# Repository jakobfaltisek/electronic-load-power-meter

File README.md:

View this project on [CADLAB.io](https://cadlab.io/project/1274). 

# electronic-load-power-meter

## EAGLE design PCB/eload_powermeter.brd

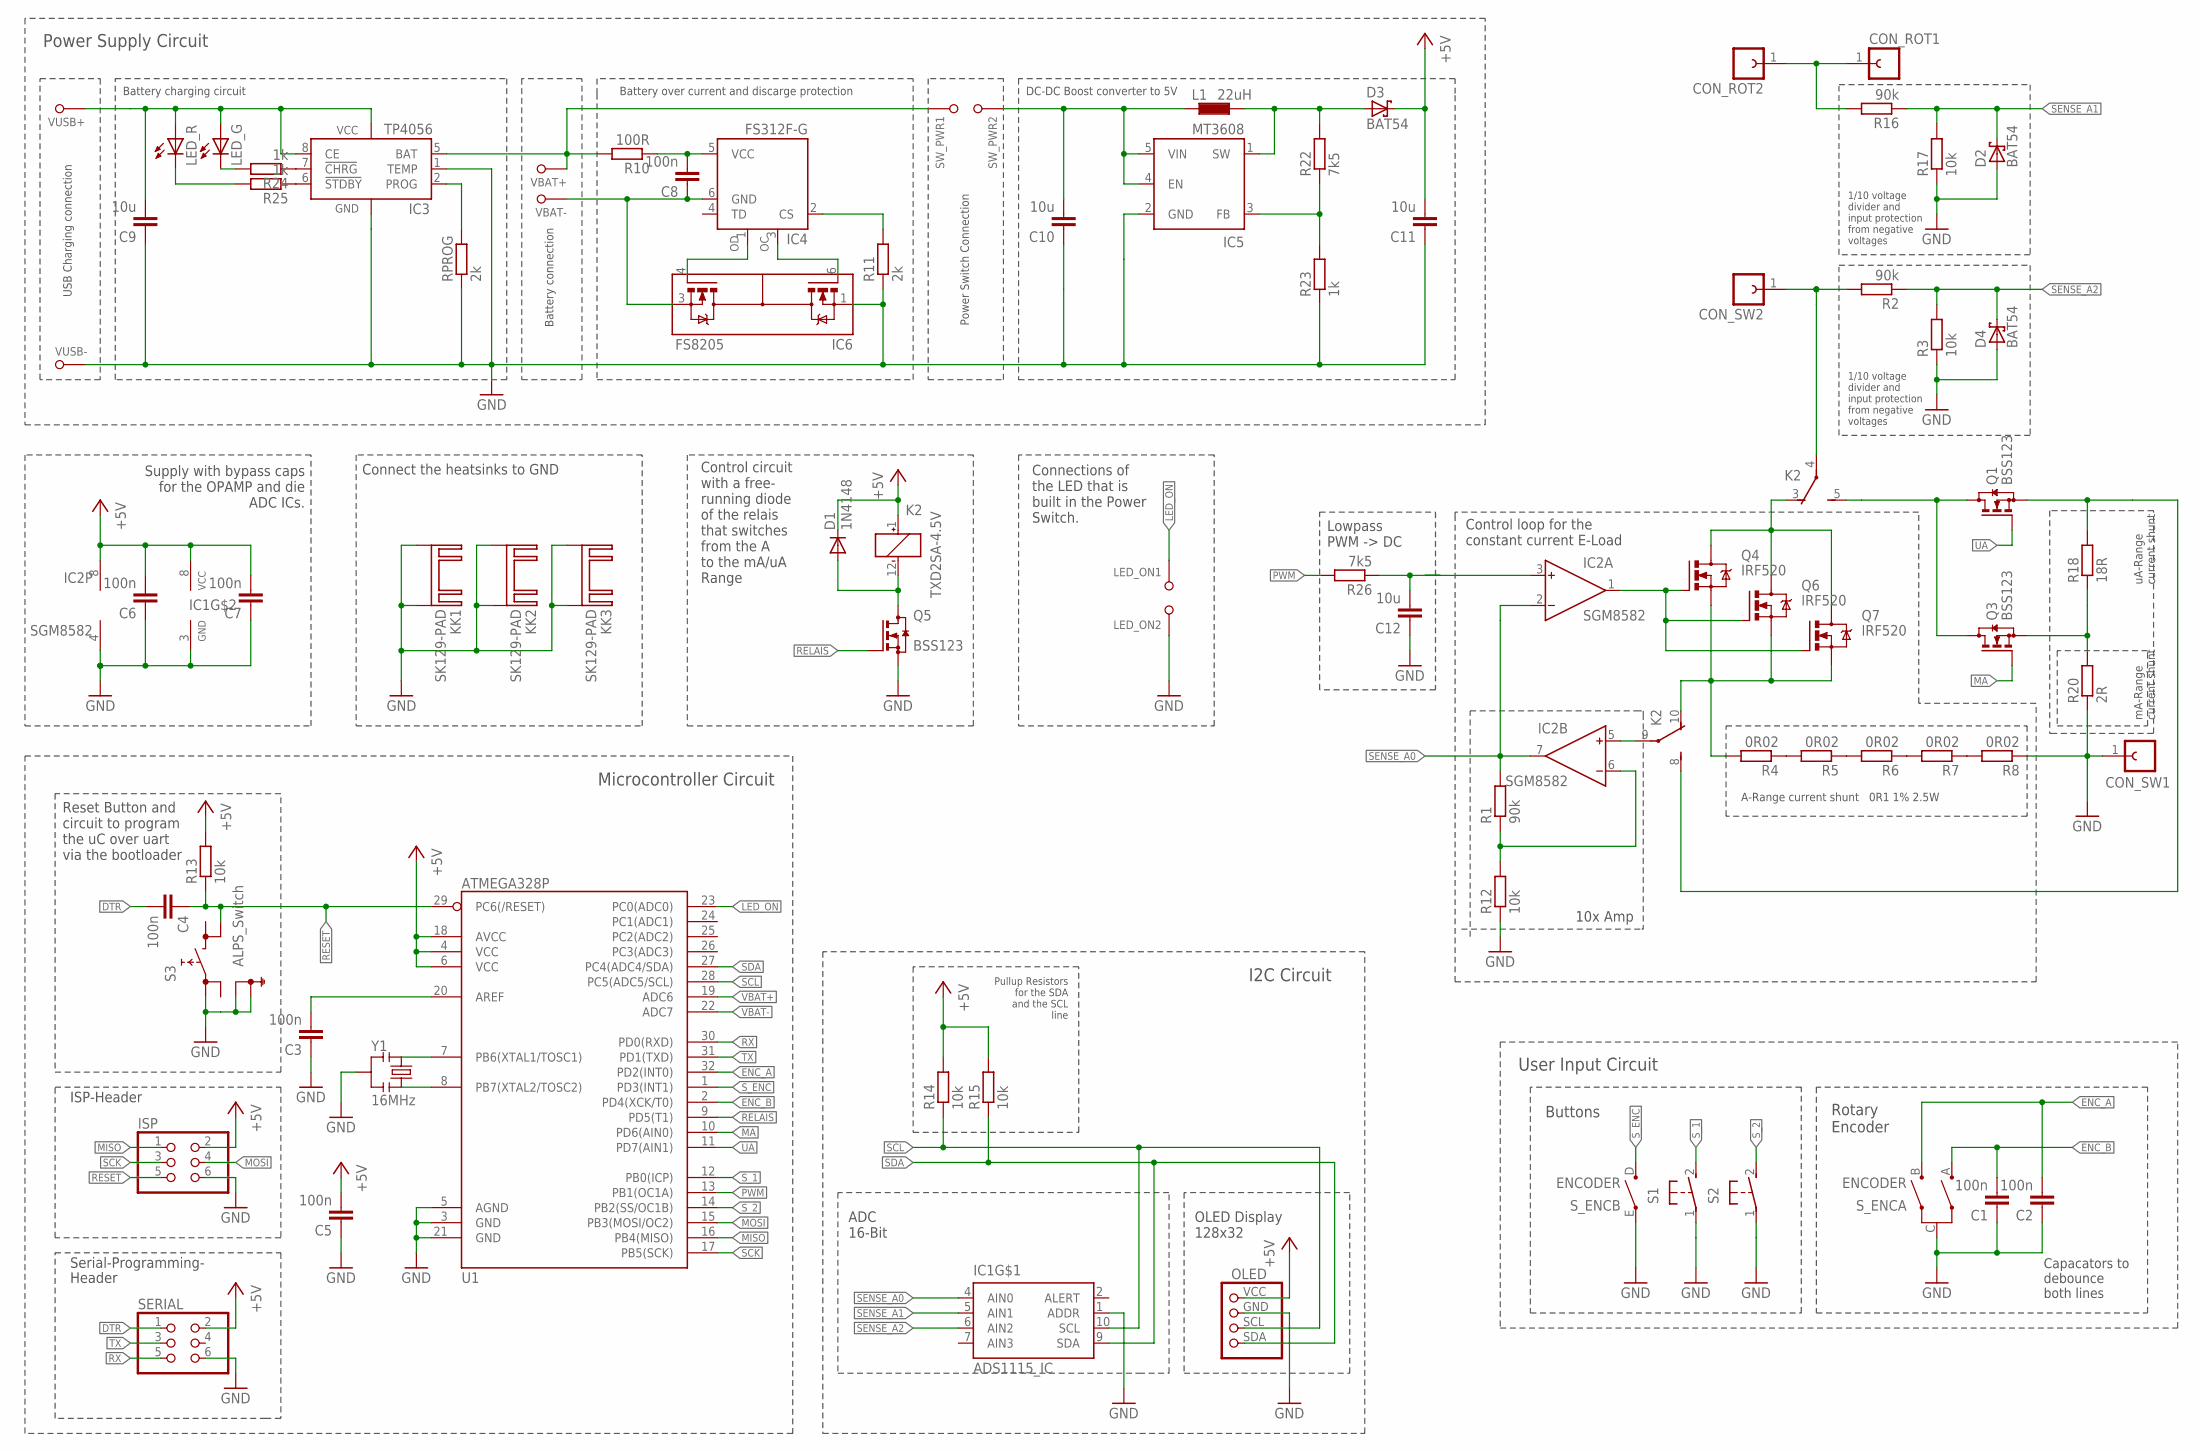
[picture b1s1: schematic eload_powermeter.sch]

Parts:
C1, C2, C3, C4, C5, C6, C7, C8: 100n; C0603
C9, C10, C11, C12: 10u; C0603
CON_ROT1, CON_ROT2: BANANEN_BUCHSE; BANANENBUCHSE
CON_SW1, CON_SW2: BANANEN_BUCHSE; BANANENBUCHSE
D1: 1N4148; SOD123
D2, D3, D4: BAT54; SOT23
IC1: ADS1115_IC; MSOP10
IC2: SGM8582; SO8
IC3: TP4056; SOP08
IC4: FS312F-G; SOT23-6
IC5: MT3608; SOT23-6
IC6: FS8205; SOT23-6
ISP: PINHD-2X3_SMD; 2X03
K2: TXD2SA-4.5V; TXD2SA
KK1, KK2, KK3: SK129-PAD; SK129
L1: 22uH; R1210
LED_G: LED_REVERSE_MOUNTSMT1206_REVERSE; 1206_LED_REVERSE_MOUNT
LED_ON1, LED_ON2: SOLDER_PAD
LED_R: LED_REVERSE_MOUNTSMT1206_REVERSE; 1206_LED_REVERSE_MOUNT
OLED: OLED_128X32; 1X04_OLED
Q1, Q3, Q5: BSS123; SOT23
Q4, Q6, Q7: IRF520; TO220BV
R1, R2, R16: 90k; R0603
R3, R12, R13, R14, R15, R17: 10k; R0603
R4, R5, R6, R7, R8: 0R02; R1206
R10: 100R; R0603
R11: 2k; R0603
R18: 18R; R0603
R20: 2R; R0603
R22, R26: 7k5; R0603
R23, R24, R25: 1k; R0603
RPROG: 2k; R0603
S1, S2: PUSH_BUTTON_ALPS; B3F-31XX
S3: ALPS_Switch; SKHMPXE010
SERIAL: PINHD-2X3_SMD; 2X03
SW_PWR1, SW_PWR2: SOLDER_PAD
S_ENC: ENCODER; CI-11
U1: ATMEGA328P; TQFP32-08
VBAT+: SOLDER_PAD
VBAT-: SOLDER_PAD
VUSB+: SOLDER_PAD
VUSB-: SOLDER_PAD
Y1: 16MHz; RESONATOR-SMD-1:1

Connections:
+5V: C5.2, C6.2, C7.2, C11.2, D1.C, D3.3 (C), IC1.8 (VCC), IC2.8 (V+), ISP.2, K2.1 (+), OLED.VCC (VDD), R13.2, R14.2, R15.2, SERIAL.2, U1.4 (VCC), U1.6 (VCC), U1.18 (AVCC)
DTR: C4.2, SERIAL.1
ENC_A: C2.2, S_ENC.B, U1.32 (PD2(INT0))
ENC_B: C1.2, S_ENC.A, U1.2 (PD4(XCK/T0))
GND: C1.1, C2.1, C3.1, C5.1, C6.1, C7.1, C9.1, C10.1, C11.1, C12.1, CON_SW1.1, D2.1 (A), D4.1 (A), IC1.1 (ADDR), IC1.3 (GND), IC2.4 (V-), IC3.1 (TEMP), IC3.3 (GND), IC5.2 (GND), IC6.1 (S1), ISP.6, KK1.A2,5, KK1.B2,5, KK2.A2,5, KK2.B2,5, KK3.A2,5, KK3.B2,5, LED_ON2.P$1, OLED.GND, Q5.2 (S), R3.1, R8.1, R11.1, R12.1, R17.1, R20.1, R23.1, RPROG.1, S1.1, S2.1, S3.1 (3.1), S3.5 (SH1), S3.6 (SH2), SERIAL.6, S_ENC.C, S_ENC.E, U1.3 (GND), U1.5 (AGND), U1.21 (GND), VUSB-.P$1, Y1.2
LED_ON: LED_ON1.P$1, U1.23 (PC0(ADC0))
MA: Q3.1 (G), U1.10 (PD6(AIN0))
MISO: ISP.1, U1.16 (PB4(MISO))
MOSI: ISP.4, U1.15 (PB3(MOSI/OC2))
unnamed: CON_ROT1.1, CON_ROT2.1, R16.2
unnamed: IC2.1 (OUT), Q4.G, Q6.G, Q7.G
unnamed: Q3.2 (S), R18.1, R20.2
unnamed: K2.5 (S), Q1.3 (D), Q3.3 (D)
unnamed: R4.1, R5.2
unnamed: K2.10 (O), Q4.S, Q6.S, Q7.S, R4.2
unnamed: C12.2, IC2.3 (IN+), R26.1
unnamed: K2.3 (O), Q4.D, Q6.D, Q7.D
unnamed: D1.A, K2.12 (-), Q5.3 (D)
unnamed: R5.1, R6.2
unnamed: U1.7 (PB6(XTAL1/TOSC1)), Y1.1
unnamed: IC2.5 (IN+), K2.9
unnamed: CON_SW2.1, K2.4, R2.2
unnamed: U1.8 (PB7(XTAL2/TOSC2)), Y1.3
unnamed: C8.2, IC4.5 (VCC), R10.1
unnamed: R6.1, R7.2
unnamed: R7.1, R8.2
unnamed: D3.1 (A), IC5.1 (SW), L1.2, R22.2
unnamed: IC4.1 (OD), IC6.4 (G2)
unnamed: IC3.2 (PROG), RPROG.2
unnamed: IC4.3 (OC), IC6.6 (G1)
unnamed: C10.2, IC5.4 (EN), IC5.5 (VIN), L1.1, SW_PWR2.P$1
unnamed: IC4.2 (CS), R11.2
unnamed: IC5.3 (FB), R22.1, R23.2
unnamed: IC3.7 (!CHRG), R24.1
unnamed: IC3.6 (!STDBY), R25.1
unnamed: LED_G.C, R24.2
unnamed: LED_R.C, R25.2
unnamed: C3.2, U1.20 (AREF)
unnamed: IC2.6 (IN-), R1.1, R12.2
unnamed: K2.8 (S), Q1.2 (S), R18.2
PWM: R26.2, U1.13 (PB1(OC1A))
RELAIS: Q5.1 (G), U1.9 (PD5(T1))
RESET: C4.1, ISP.5, R13.1, S3.4 (4.2), U1.29 (PC6(/RESET))
RX: SERIAL.5, U1.30 (PD0(RXD))
SCK: ISP.3, U1.17 (PB5(SCK))
SCL: IC1.10 (SCL), OLED.SCL, R14.1, U1.28 (PC5(ADC5/SCL))
SDA: IC1.9 (SDA), OLED.SDA, R15.1, U1.27 (PC4(ADC4/SDA))
SENSE_A0: IC1.4 (AIN0), IC2.2 (IN-), IC2.7 (OUT), R1.2
SENSE_A1: D2.3 (C), IC1.5 (AIN1), R16.1, R17.2
SENSE_A2: D4.3 (C), IC1.6 (AIN2), R2.1, R3.2
S_1: S1.2 (S), U1.12 (PB0(ICP))
S_2: S2.2 (S), U1.14 (PB2(SS/OC1B))
S_ENC: S_ENC.D, U1.1 (PD3(INT1))
TX: SERIAL.3, U1.31 (PD1(TXD))
UA: Q1.1 (G), U1.11 (PD7(AIN1))
VBAT+: IC3.5 (BAT), R10.2, SW_PWR1.P$1, U1.19 (ADC6), VBAT+.P$1
VBAT-: C8.1, IC4.6 (GND), IC6.3 (S2), U1.22 (ADC7), VBAT-.P$1
VUSB: C9.2, IC3.4 (VCC), IC3.8 (CE), LED_G.A, LED_R.A, VUSB+.P$1

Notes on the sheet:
Microcontroller Circuit
ISP-Header
Serial-Programming-
Header
10x Amp
Lowpass PWM -> DC
1/10 voltage divider and input protection from negative voltages
A-Range current shunt 0R1 1% 2.5W
mA-Range current shunt
uA-Range current shunt
Control loop for the constant current E-Load
Reset Button and circuit to program the uC over uart via the bootloader
Supply with bypass caps for the OPAMP and die ADC ICs.
Connect the heatsinks to GND
Control circuit with a free- running diode of the relais that switches from the A to the mA/uA Range
Battery charging circuit
Battery over current and discarge protection
DC-DC Boost converter to 5V
USB Charging connection
Battery connection
Power Switch Connection
Power Supply Circuit
I2C Circuit
Pullup Resistors for the SDA and the SCL line
ADC 16-Bit
OLED Display 128x32
Buttons
Rotary Encoder
User Input Circuit
Capacators to debounce both lines
Connections of the LED that is built in the Power Switch.

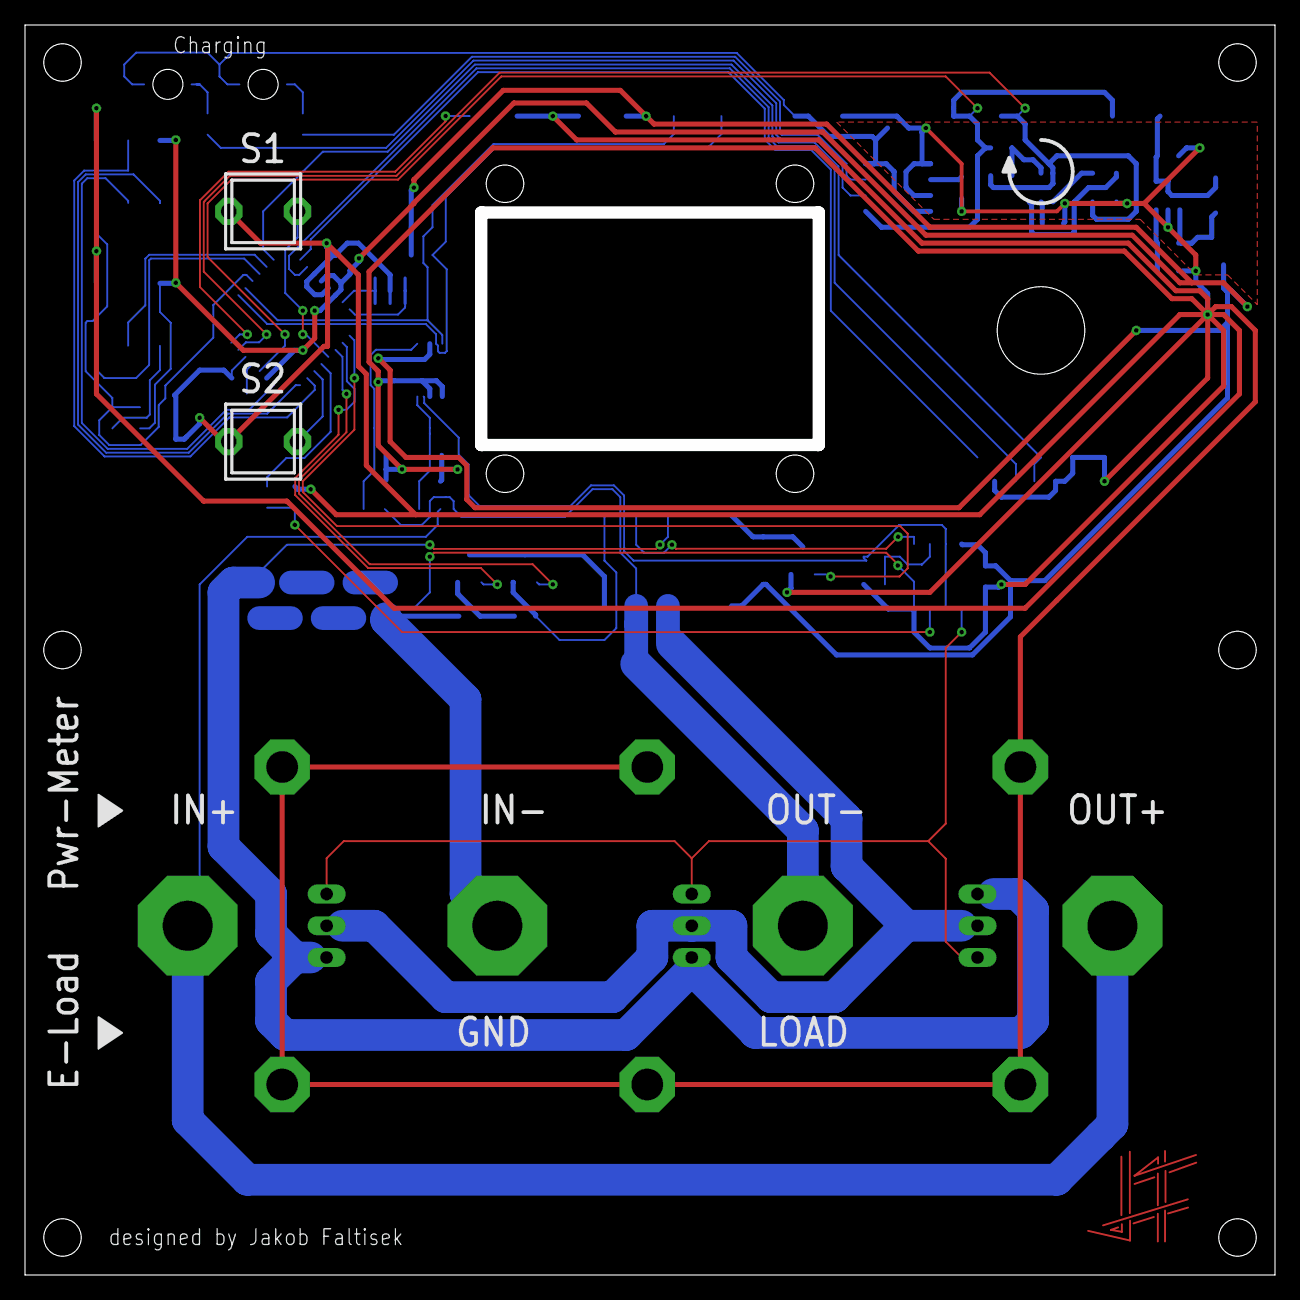
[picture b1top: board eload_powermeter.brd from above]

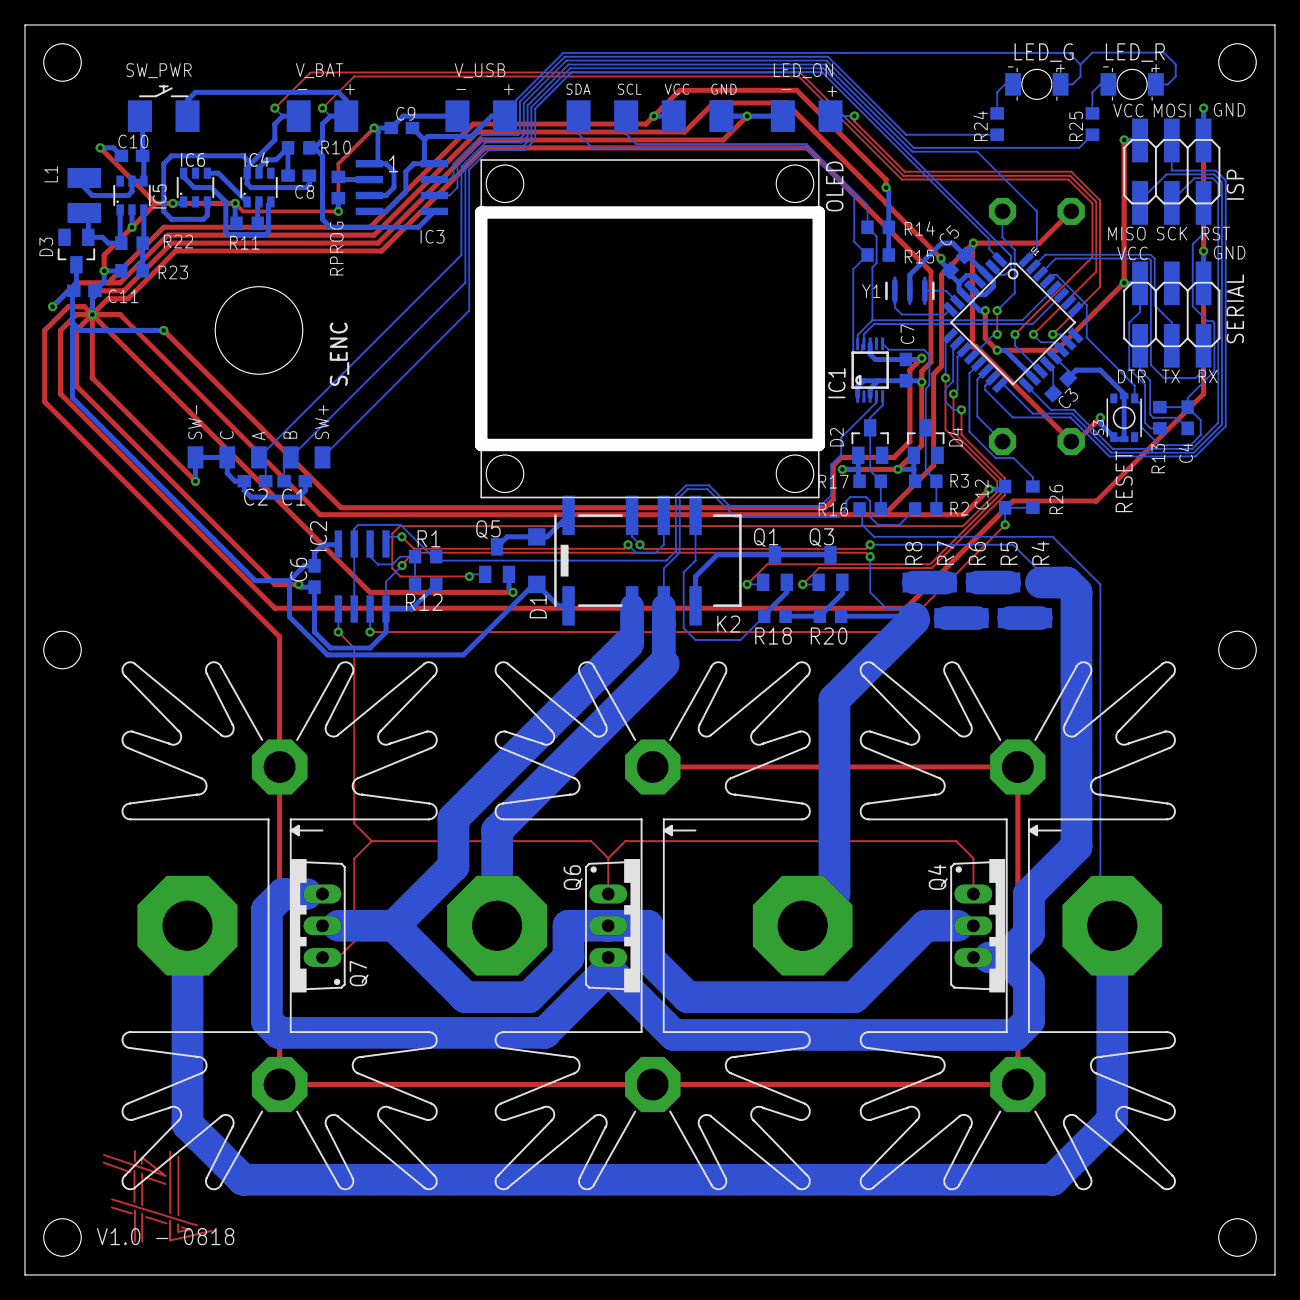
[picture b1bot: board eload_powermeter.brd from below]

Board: 2 copper layers, 100.0 x 100.0 mm, 80 parts (72 on the bottom side), 58 nets.

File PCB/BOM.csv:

"Part";"Value";"Device";"Package";"Description";"MF";"MPN";"OC_FARNELL";"OC_NEWARK";"SPICEPREFIX";
"C1";"100n";"C-EUC0603";"C0603";"CAPACITOR, European symbol";"";"";"";"";"C";
"C2";"100n";"C-EUC0603";"C0603";"CAPACITOR, European symbol";"";"";"";"";"C";
"C3";"100n";"C-EUC0603";"C0603";"CAPACITOR, European symbol";"";"";"";"";"C";
"C4";"100n";"C-EUC0603";"C0603";"CAPACITOR, European symbol";"";"";"";"";"C";
"C5";"100n";"C-EUC0603";"C0603";"CAPACITOR, European symbol";"";"";"";"";"C";
"C6";"100n";"C-EUC0603";"C0603";"CAPACITOR, European symbol";"";"";"";"";"C";
"C7";"100n";"C-EUC0603";"C0603";"CAPACITOR, European symbol";"";"";"";"";"C";
"C8";"100n";"C-EUC0603";"C0603";"CAPACITOR, European symbol";"";"";"";"";"C";
"C9";"10u";"C-EUC0603";"C0603";"CAPACITOR, European symbol";"";"";"";"";"C";
"C10";"10u";"C-EUC0603";"C0603";"CAPACITOR, European symbol";"";"";"";"";"C";
"C11";"10u";"C-EUC0603";"C0603";"CAPACITOR, European symbol";"";"";"";"";"C";
"C12";"10u";"C-EUC0603";"C0603";"CAPACITOR, European symbol";"";"";"";"";"C";
"CON_ROT1";"";"BANANEN_BUCHSE";"BANANENBUCHSE";"FEMALE HEADER";"";"";"";"";"";
"CON_ROT2";"";"BANANEN_BUCHSE";"BANANENBUCHSE";"FEMALE HEADER";"";"";"";"";"";
"CON_SW1";"";"BANANEN_BUCHSE";"BANANENBUCHSE";"FEMALE HEADER";"";"";"";"";"";
"CON_SW2";"";"BANANEN_BUCHSE";"BANANENBUCHSE";"FEMALE HEADER";"";"";"";"";"";
"D1";"1N4148";"MBR0520LT";"SOD123";"SCHOTTKY BARRIER RECTIFIER";"";"";"";"";"";
"D2";"BAT54";"BAT54";"SOT23";"Schottky Diodes";"";"";"";"";"";
"D3";"BAT54";"BAT54";"SOT23";"Schottky Diodes";"";"";"";"";"";
"D4";"BAT54";"BAT54";"SOT23";"Schottky Diodes";"";"";"";"";"";
"IC1";"ADS1115_IC";"ADS1115_IC";"MSOP10";"edit this description";"";"";"";"";"";
"IC2";"SGM8582";"AD826R";"SO8";"High-Speed, Low-Power Dual Operational Amplifier";"ALTERA CORPORATION";"AD826AR";"1651291";"05F7688";"";
"IC3";"TP4056";"TP4056";"SOP08";"edit this description";"";"";"";"";"";
"IC4";"FS312F-G";"FS312F-G";"SOT23-6";"edit this description";"";"";"";"";"";
"IC5";"MT3608";"MT3608";"SOT23-6";"90% EFFICIENT SYNCHRONOUS BOOST CONVERTER WITH 600-mA SWITCH";"";"";"";"";"";
"IC6";"FS8205";"FS8205";"SOT23-6";"";"";"";"";"";"";
"ISP";"";"PINHD-2X3_SMD";"2X03";"PIN HEADER";"";"";"";"";"";
"K2";"TXD2SA-4.5V";"TXD2SA-4.5V";"TXD2SA";"TX Relais NAiS";"";"TXD2SA-4.5V";"unknown";"13P9531";"";
"KK1";"SK129-PAD";"SK129-PAD";"SK129";"HEATSINK manufacturer Fischer/distributor Buerklin";"";"";"";"";"";
"KK2";"SK129-PAD";"SK129-PAD";"SK129";"HEATSINK manufacturer Fischer/distributor Buerklin";"";"";"";"";"";
"KK3";"SK129-PAD";"SK129-PAD";"SK129";"HEATSINK manufacturer Fischer/distributor Buerklin";"";"";"";"";"";
"L1";"22uH";"L_1210";"R1210";"";"";"";"";"";"";
"LED_G";"";"LED_REVERSE_MOUNTSMT1206_REVERSE";"1206_LED_REVERSE_MOUNT";"LED";"";"";"";"";"";
"LED_ON1";"SOLDER_PAD";"SOLDER_PAD";"SOLDER_PAD";"";"";"";"";"";"";
"LED_ON2";"SOLDER_PAD";"SOLDER_PAD";"SOLDER_PAD";"";"";"";"";"";"";
"LED_R";"";"LED_REVERSE_MOUNTSMT1206_REVERSE";"1206_LED_REVERSE_MOUNT";"LED";"";"";"";"";"";
"OLED";"";"OLED_128X32";"1X04_OLED";"PIN HEADER";"";"";"";"";"";
"Q1";"BSS123";"BSS123";"SOT23";"N-CHANNEL MOS FET";"";"";"";"";"";
"Q3";"BSS123";"BSS123";"SOT23";"N-CHANNEL MOS FET";"";"";"";"";"";
"Q4";"IRF520";"IRF520";"TO220BV";"HEXFET Power MOSFET";"";"";"";"";"";
"Q5";"BSS123";"BSS123";"SOT23";"N-CHANNEL MOS FET";"";"";"";"";"";
"Q6";"IRF520";"IRF520";"TO220BV";"HEXFET Power MOSFET";"";"";"";"";"";
"Q7";"IRF520";"IRF520";"TO220BV";"HEXFET Power MOSFET";"";"";"";"";"";
"R1";"90k";"R-EU_R0603";"R0603";"RESISTOR, European symbol";"";"";"";"";"R";
"R2";"90k";"R-EU_R0603";"R0603";"RESISTOR, European symbol";"";"";"";"";"R";
"R3";"10k";"R-EU_R0603";"R0603";"RESISTOR, European symbol";"";"";"";"";"R";
"R4";"0R02";"R-EU_R1206";"R1206";"RESISTOR, European symbol";"";"";"";"";"R";
"R5";"0R02";"R-EU_R1206";"R1206";"RESISTOR, European symbol";"";"";"";"";"R";
"R6";"0R02";"R-EU_R1206";"R1206";"RESISTOR, European symbol";"";"";"";"";"R";
"R7";"0R02";"R-EU_R1206";"R1206";"RESISTOR, European symbol";"";"";"";"";"R";
"R8";"0R02";"R-EU_R1206";"R1206";"RESISTOR, European symbol";"";"";"";"";"R";
"R10";"100R";"R-EU_R0603";"R0603";"RESISTOR, European symbol";"";"";"";"";"R";
"R11";"2k";"R-EU_R0603";"R0603";"RESISTOR, European symbol";"";"";"";"";"R";
"R12";"10k";"R-EU_R0603";"R0603";"RESISTOR, European symbol";"";"";"";"";"R";
"R13";"10k";"R-EU_R0603";"R0603";"RESISTOR, European symbol";"";"";"";"";"R";
"R14";"10k";"R-EU_R0603";"R0603";"RESISTOR, European symbol";"";"";"";"";"R";
"R15";"10k";"R-EU_R0603";"R0603";"RESISTOR, European symbol";"";"";"";"";"R";
"R16";"90k";"R-EU_R0603";"R0603";"RESISTOR, European symbol";"";"";"";"";"R";
"R17";"10k";"R-EU_R0603";"R0603";"RESISTOR, European symbol";"";"";"";"";"R";
"R18";"18R";"R-EU_R0603";"R0603";"RESISTOR, European symbol";"";"";"";"";"R";
"R20";"2R";"R-EU_R0603";"R0603";"RESISTOR, European symbol";"";"";"";"";"R";
"R22";"7k5";"R-EU_R0603";"R0603";"RESISTOR, European symbol";"";"";"";"";"R";
"R23";"1k";"R-EU_R0603";"R0603";"RESISTOR, European symbol";"";"";"";"";"R";
"R24";"1k";"R-EU_R0603";"R0603";"RESISTOR, European symbol";"";"";"";"";"R";
"R25";"1k";"R-EU_R0603";"R0603";"RESISTOR, European symbol";"";"";"";"";"R";
"R26";"7k5";"R-EU_R0603";"R0603";"RESISTOR, European symbol";"";"";"";"";"R";
"RPROG";"2k";"R-EU_R0603";"R0603";"RESISTOR, European symbol";"";"";"";"";"R";
"S1";"";"PUSH_BUTTON_ALPS";"B3F-31XX";"OMRON SWITCH";"";"B3F-3100";"959704";"36M3582";"";
"S2";"";"PUSH_BUTTON_ALPS";"B3F-31XX";"OMRON SWITCH";"";"B3F-3100";"959704";"36M3582";"";
"S3";"ALPS_Switch";"ALPS_SKSGPAE010S";"SKHMPXE010";"6.2 X 6.5mm TACT Switch (SMD)";"";"";"";"";"";
"SERIAL";"";"PINHD-2X3_SMD";"2X03";"PIN HEADER";"";"";"";"";"";
"SW_PWR1";"SOLDER_PAD";"SOLDER_PAD";"SOLDER_PAD";"";"";"";"";"";"";
"SW_PWR2";"SOLDER_PAD";"SOLDER_PAD";"SOLDER_PAD";"";"";"";"";"";"";
"S_ENC";"ENCODER";"ENCODER";"CI-11";"11mm Incemental Encoder";"";"";"unknown";"unknown";"";
"U1";"ATMEGA328P";"ATMEGA328P";"TQFP32-08";"";"";"";"";"";"";
"VBAT+";"SOLDER_PAD";"SOLDER_PAD";"SOLDER_PAD";"";"";"";"";"";"";
"VBAT-";"SOLDER_PAD";"SOLDER_PAD";"SOLDER_PAD";"";"";"";"";"";"";
"VUSB+";"SOLDER_PAD";"SOLDER_PAD";"SOLDER_PAD";"";"";"";"";"";"";
"VUSB-";"SOLDER_PAD";"SOLDER_PAD";"SOLDER_PAD";"";"";"";"";"";"";
"Y1";"16MHz";"RESONATOR1:1";"RESONATOR-SMD-1:1";"Resonator";"";"";"";"";"";

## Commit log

2018-08-05 starting point
    starting point of the PCB
2018-08-05 Parts in lib, parts of the schematic
    Creating the footprints in the library for the used parts. Starting with the schematic.
2018-08-10 finish boost circuit, start reverse surface mount led
    Finishing the boost converter circuit and selecting the inductor and the schottky diode.
    Starting with the footprint of the reverse surface mount led.
2018-08-12 Current Sense Schematic, Switching a few components
    Working on the current sense schematic. Cleaning up some other parts. Switching a few components/footprints - primariliy the footprint of the oled screen.
2018-08-15 Finishing Schematic, Starting with Layout
    Finishing and cleaning up the schematic, but also replacing some components and optimizing some footprints, for example the ATmega.
    Starting with the PCB Layout - placing the components, wiring up the power circuit and the power cuircuit.
    Adding an excel file, which shows the data of the chosen values of the current shunt resistors.
2018-08-19 Finish Layout, document schematic with blocks
    Routing the last connections of the layout. Starting with the naming on the top panel.
    Documenting the schematic by adding functional blocks and descriping them.
2018-08-21 Adding some missing uC connections.
    Adding some connections of the uC that were missing before.
2018-08-25 Adding Battery measurement and power on led. Cleaning up silk screen.
    Connecting both terminals of the battery to adc pins of the uC to measure the battery capacity. Adding the connections of the power-on led that is build in to the button.
    Cleaning up the component names of the silk screen.
2018-08-28 Final V1.0 Production Version
    Finalising the V1.0 Production Version.
    Generationg the gerbers and the BOM
2018-09-01 Backlink to CADLAB.io has been added.
